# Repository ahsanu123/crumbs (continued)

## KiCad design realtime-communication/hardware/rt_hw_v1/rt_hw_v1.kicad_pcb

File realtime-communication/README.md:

## SDMMC and SDIO 

[See Kicad Project](https://kicanvas.org/?repo=https%3A%2F%2Fgithub.com%2Fahsanu123%2Fcrumbs%2Ftree%2Fmain%2Frealtime-communication%2Fhardware%2Frt_hw_v1)

SDMMC is hardware host, and SDIO is the protocol. 

- look at esp32 [SDMMC documentation here](https://docs.espressif.com/projects/rust/esp-hal/1.2.0/esp32s3/esp_hal/sdmmc/index.html)
- working POC in STM32F407VGT6 is use this _file system_ [exfat-slim](https://github.com/ninjasource/exfat-slim/tree/main),
  poc already prof library able to reading and writing into file. 
- make sure to format sdcard to exfat file system, use this command below, make sure you install required dependencies 
  - install with pacman `sudo pacman -S exfatprogs parted dosfstools `
  - use `lsblk` to list all possible sdcard
  - replace _X_ to possible sdcard listed from lsblk 
  - `sudo umount /dev/sdX*`
  - `sudo wipefs -a /dev/sdX`
  - `sudo parted /dev/sdX --script mklabel msdos`
  - `sudo parted /dev/sdX --script mkpart primary 1MiB 100%`
  - `sudo mkfs.exfat -n SDCARD /dev/sdX1`
  - `sync`
  - then check with, make sure you see exfat on command result
  - `lsblk -f /dev/sdX`
  - `sudo file -s /dev/sdX1`

## Reference 

- https://github.com/zpg6/esp32-sdcard/
- https://docs.rs/embedded-sdmmc/latest/embedded_sdmmc/
- https://github.com/ninjasource/exfat-slim/tree/main
- https://github.com/embassy-rs/sdio

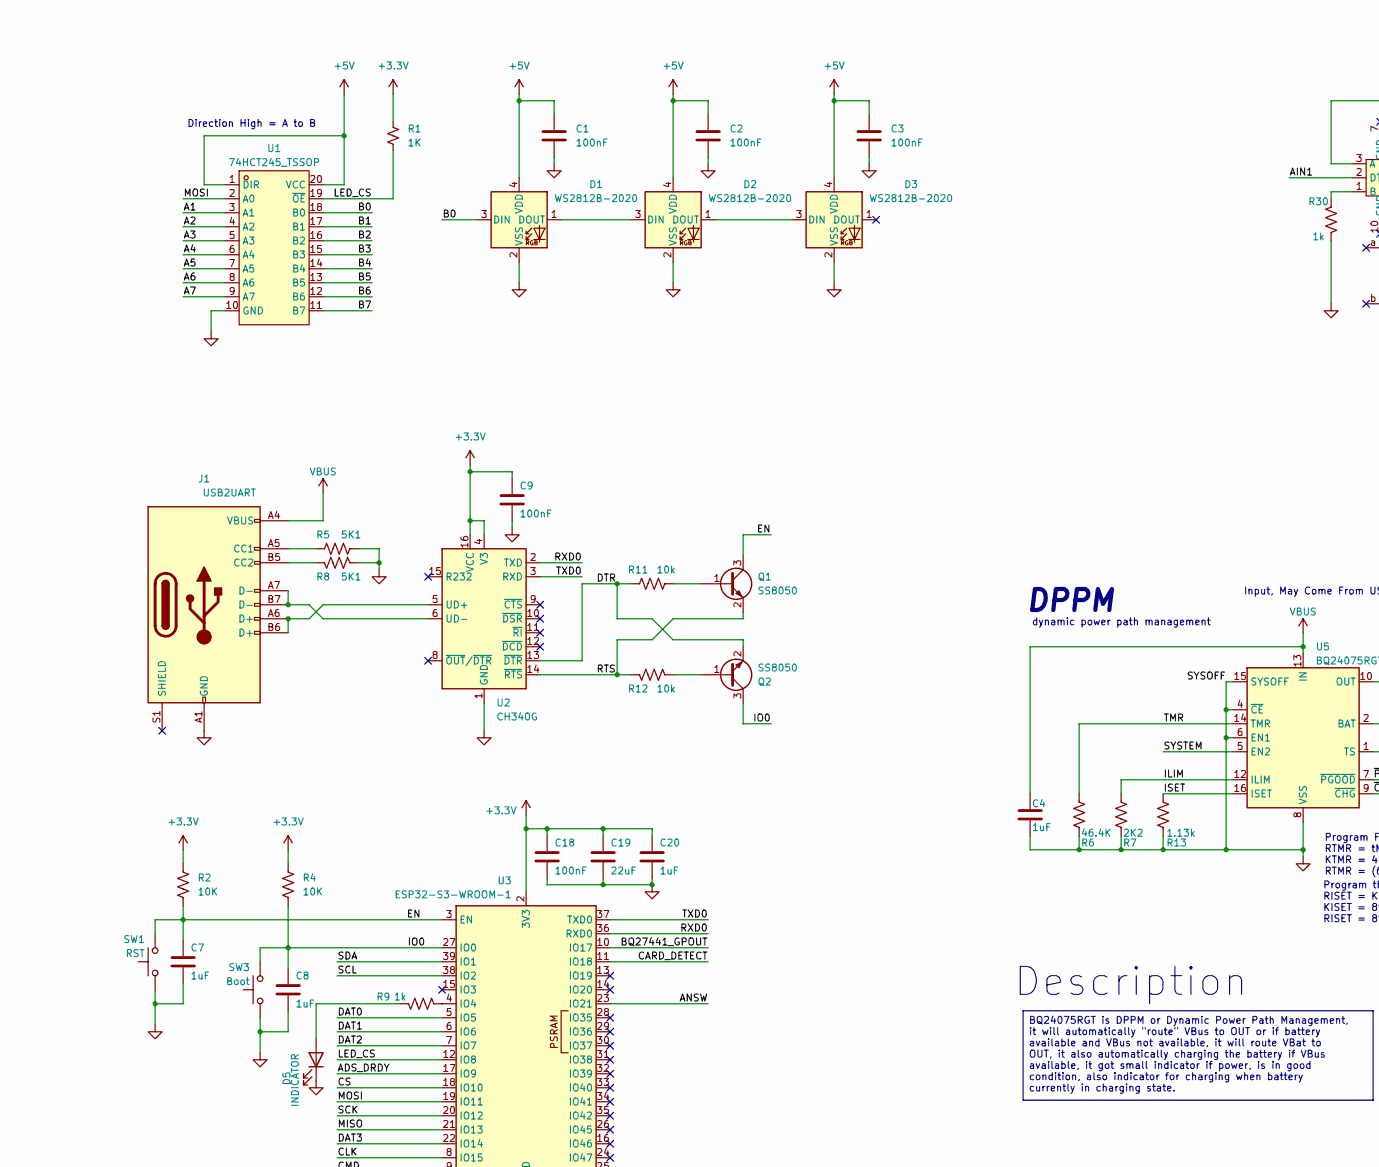
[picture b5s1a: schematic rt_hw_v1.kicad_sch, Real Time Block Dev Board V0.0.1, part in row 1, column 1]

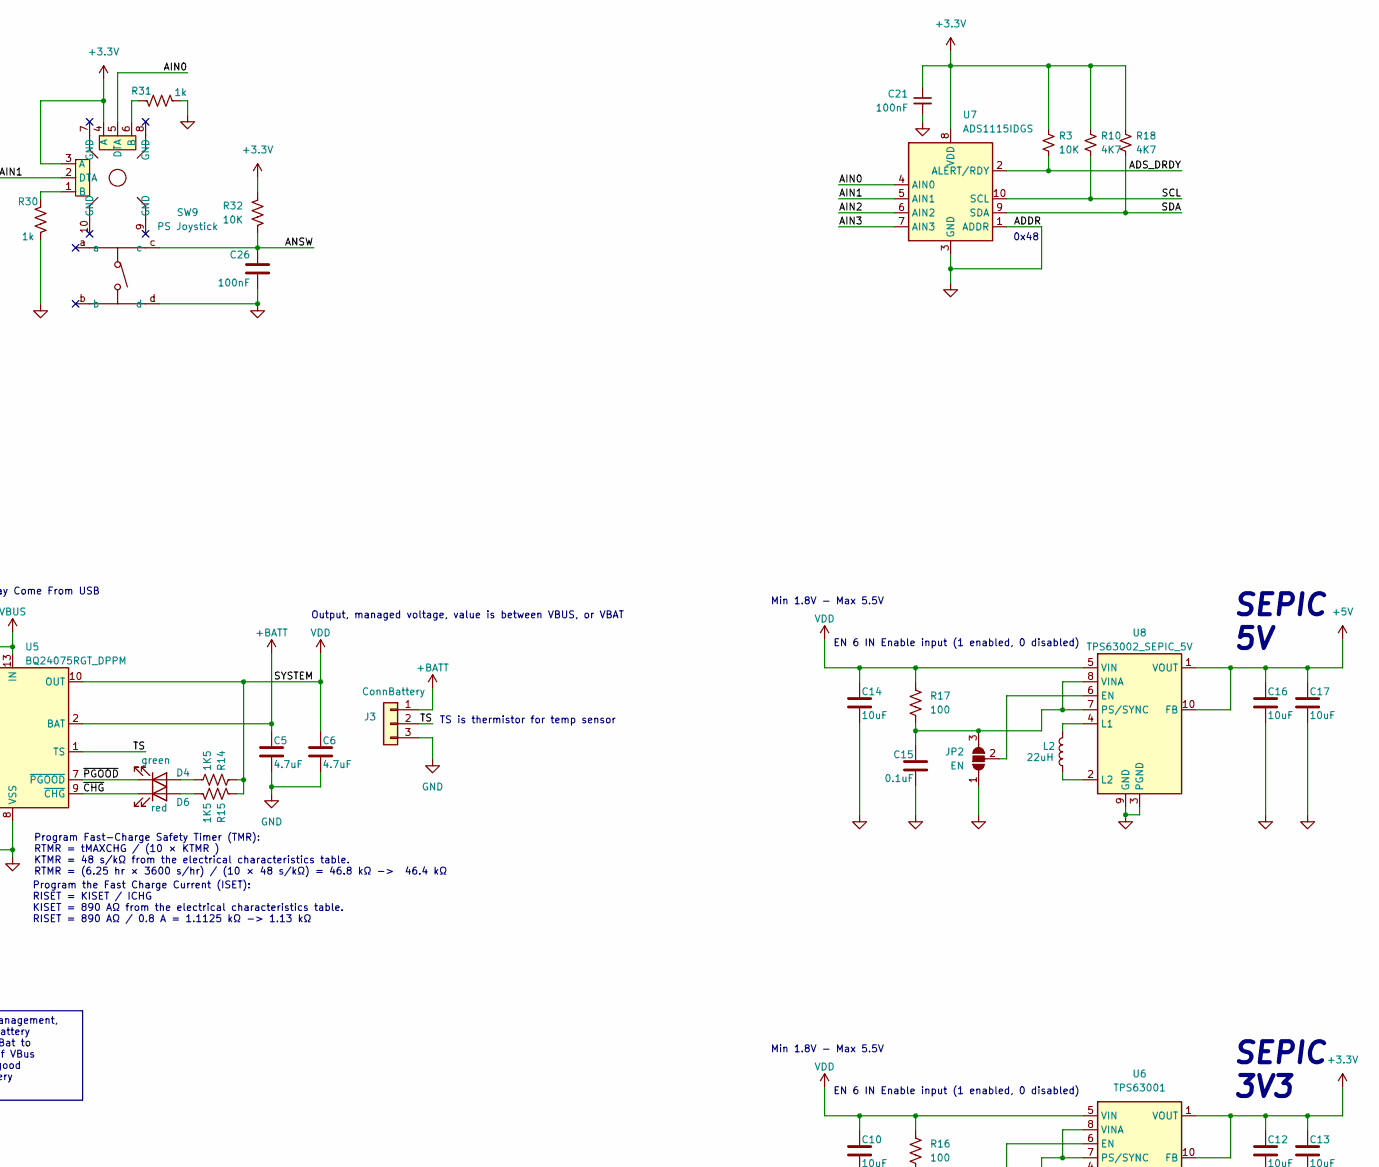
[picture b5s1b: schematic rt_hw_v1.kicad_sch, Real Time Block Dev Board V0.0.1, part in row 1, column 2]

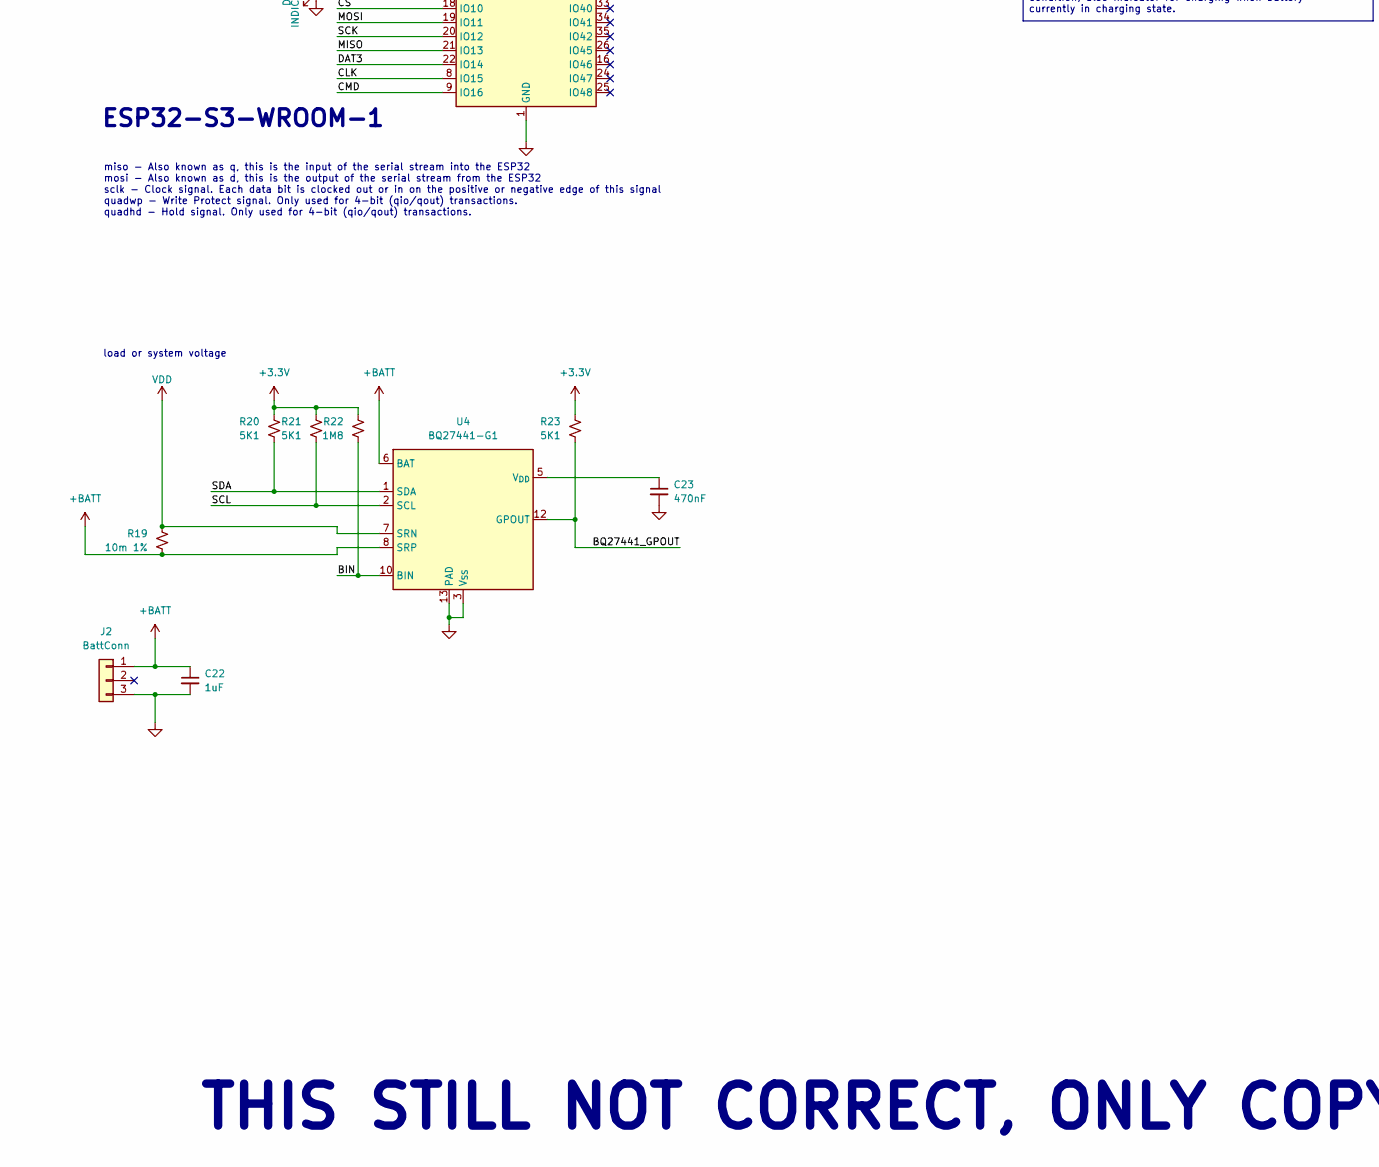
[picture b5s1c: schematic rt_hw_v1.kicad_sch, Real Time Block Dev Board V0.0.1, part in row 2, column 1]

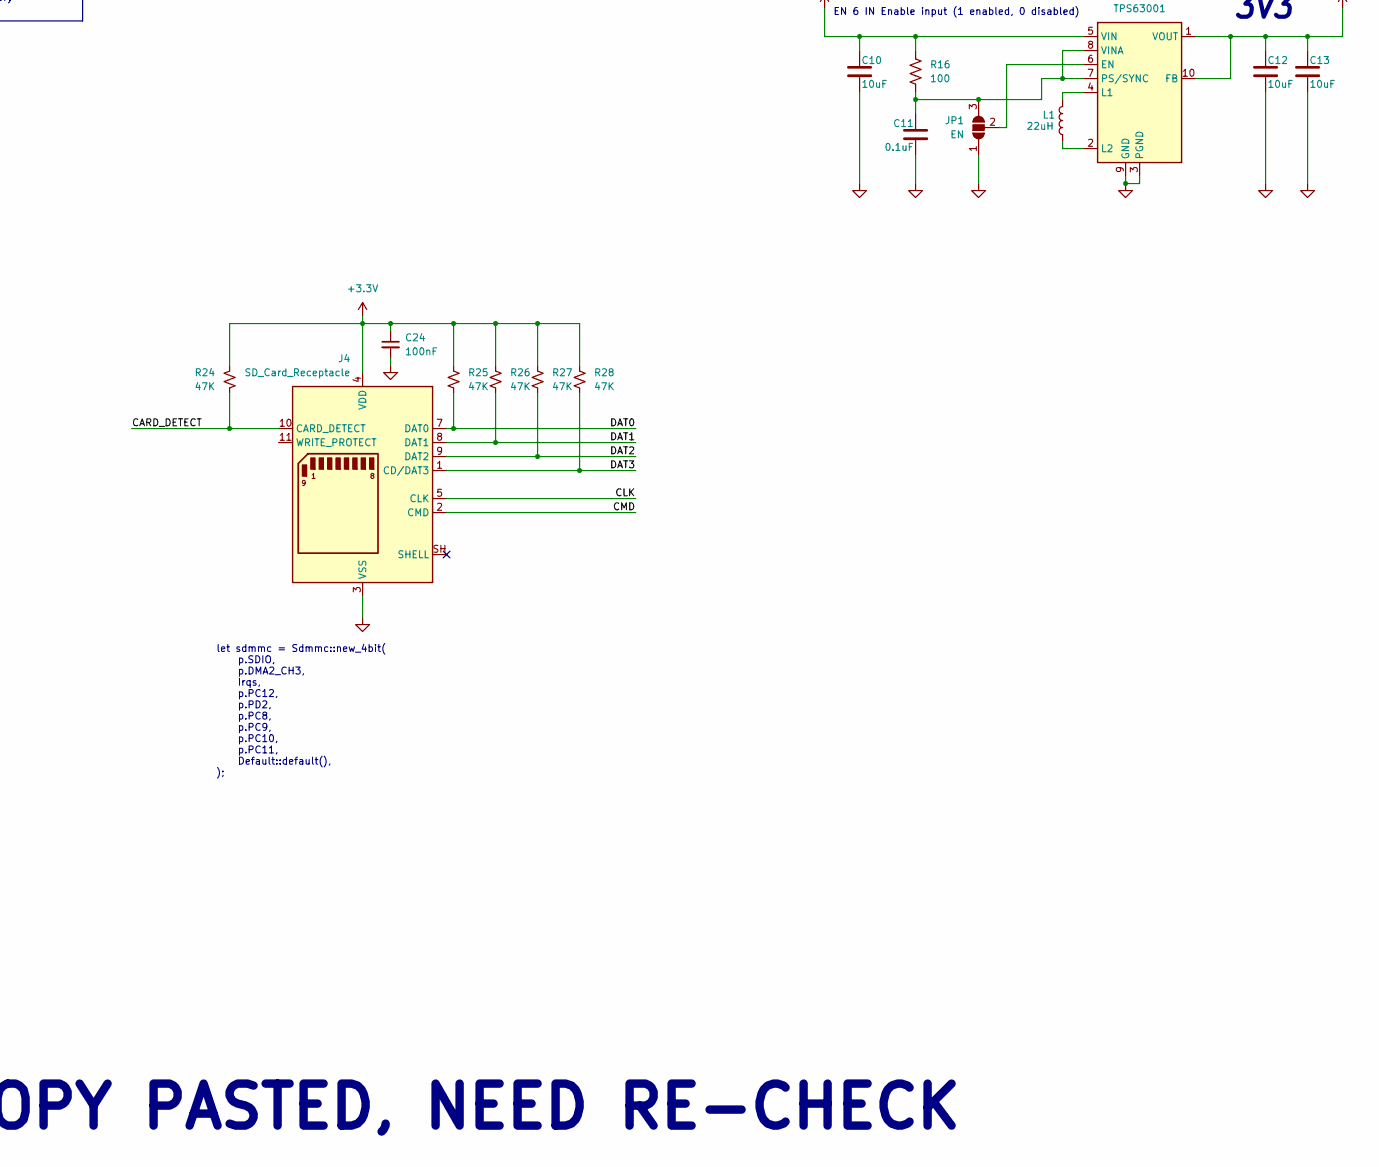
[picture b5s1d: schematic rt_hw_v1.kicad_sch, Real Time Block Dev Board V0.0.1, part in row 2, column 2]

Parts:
C1, C2, C3, C21, C24: 100nF; C_0805_2012Metric
C4, C7, C8, C20: 1uF; C_0805_2012Metric_Pad1.18x1.45mm_HandSolder
C5, C6: 4.7uF; C_0805_2012Metric_Pad1.18x1.45mm_HandSolder
C9, C18, C26: 100nF; C_0805_2012Metric_Pad1.18x1.45mm_HandSolder
C10, C12, C13, C14, C16, C17: 10uF; C_0805_2012Metric_Pad1.18x1.45mm_HandSolder
C11, C15: 0.1uF; C_0805_2012Metric_Pad1.18x1.45mm_HandSolder
C19: 22uF; C_0805_2012Metric_Pad1.18x1.45mm_HandSolder
C22: 1uF; C_0805_2012Metric
C23: 470nF; C_0805_2012Metric
D1, D2, D3: WS2812B-2020; LED_WS2812B-2020_PLCC4_2.0x2.0mm
D4: green; LED_0805_2012Metric_Pad1.15x1.40mm_HandSolder
D5: INDICATOR; LED_1206_3216Metric_Pad1.42x1.75mm_HandSolder
D6: red; LED_0805_2012Metric_Pad1.15x1.40mm_HandSolder
J1: USB2UART; USB_C_Receptacle_GCT_USB4110
J2: BattConn; PinSocket_1x03_P2.54mm_Vertical
J3: ConnBattery; PinHeader_1x03_P2.54mm_Vertical
J4: SD_Card_Receptacle; SD_TE_2041021
JP1, JP2: EN; SolderJumper-3_P1.3mm_Open_RoundedPad1.0x1.5mm_NumberLabels
L1, L2: 22uH; L_Bourns_SRP7028A_7.3x6.6mm
Q1, Q2: SS8050; SOT-23_Handsoldering
R1: 1K; R_0805_2012Metric
R2, R4, R32: 10K; R_0805_2012Metric_Pad1.20x1.40mm_HandSolder
R3: 10K; R_0805_2012Metric
R5, R8: 5K1; R_0805_2012Metric_Pad1.20x1.40mm_HandSolder
R6: 46.4K; R_0805_2012Metric_Pad1.20x1.40mm_HandSolder
R7: 2K2; R_0805_2012Metric_Pad1.20x1.40mm_HandSolder
R9, R30, R31: 1k; R_0805_2012Metric_Pad1.20x1.40mm_HandSolder
R10, R18: 4K7; R_0805_2012Metric
R11, R12: 10k; R_0805_2012Metric_Pad1.20x1.40mm_HandSolder
R13: 1.13k; R_0805_2012Metric_Pad1.20x1.40mm_HandSolder
R14, R15: 1K5; R_0805_2012Metric_Pad1.20x1.40mm_HandSolder
R16, R17: 100; R_0805_2012Metric_Pad1.20x1.40mm_HandSolder
R19: 10m 1%; R_0805_2012Metric
R20, R21, R23: 5K1; R_0805_2012Metric
R22: 1M8; R_0805_2012Metric
R24, R25, R26, R27, R28: 47K; R_0805_2012Metric
SW1: RST; SW_SPST_PTS810
SW3: Boot; SW_SPST_PTS810
SW9: PS Joystick; SW-TH_RKJXV1224005; MPN RKJXV1224005; LCSC Part C146170
U1: 74HCT245_TSSOP; TSSOP-20_L6.5-W4.4-P0.65-LS6.4-BL; MPN 74HCT245PW; LCSC Part C52140501
U2: CH340G; SOIC-16_3.9x9.9mm_P1.27mm
U3: ESP32-S3-WROOM-1
U4: BQ27441-G1; Texas_S-PDSO-N12
U5: BQ24075RGT_DPPM; VQFN-16-1EP_3x3mm_P0.5mm_EP1.6x1.6mm
U6: TPS63001; Texas_DRC0010J_ThermalVias
U7: ADS1115IDGS; TSSOP-10_3x3mm_P0.5mm
U8: TPS63002_SEPIC_5V; Texas_DRC0010J_ThermalVias

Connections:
+3.3V: C9.1, C12.1, C13.1, C18.1, C19.1, C20.1, C21.1, C24.1, J4.4 (VDD), R1.1, R2.1, R3.1, R4.1, R10.1, R18.1, R20.1, R21.1, R22.1, R23.1, R24.1, R25.1, R26.1, R27.1, R28.1, R32.1, SW9.3 (A), SW9.4 (A), U2.4 (V3), U2.16 (VCC), U3.2 (3V3), U6.1 (VOUT), U6.10 (FB), U7.8 (VDD)
+5V: C1.1, C2.1, C3.1, C16.1, C17.1, D1.4 (VDD), D2.4 (VDD), D3.4 (VDD), U1.1 (DIR), U1.20 (VCC), U8.1 (VOUT), U8.10 (FB)
+BATT: C5.1, C22.1, J2.1, J3.1, R19.2, U4.6 (BAT), U4.8 (SRP), U5.2 (BAT), U5.3 (BAT)
/A1: U1.3 (A1)
/A2: U1.4 (A2)
/A3: U1.5 (A3)
/A4: U1.6 (A4)
/A5: U1.7 (A5)
/A6: U1.8 (A6)
/A7: U1.9 (A7)
/ADS_DRDY: R3.2, U3.17 (IO9), U7.2 (ALERT/RDY)
/AIN0: SW9.5 (DTA), U7.4 (AIN0)
/AIN1: SW9.2 (DTA), U7.5 (AIN1)
/AIN2: U7.6 (AIN2)
/AIN3: U7.7 (AIN3)
/ANSW: C26.1, R32.2, SW9.c, U3.23 (IO21)
/B0: D1.3 (DIN), U1.18 (B0)
/B1: U1.17 (B1)
/B2: U1.16 (B2)
/B3: U1.15 (B3)
/B4: U1.14 (B4)
/B5: U1.13 (B5)
/B6: U1.12 (B6)
/B7: U1.11 (B7)
/BIN: R22.2, U4.10 (BIN)
/BQ27441_GPOUT: R23.2, U3.10 (IO17), U4.12 (GPOUT)
/CARD_DETECT: J4.10 (CARD_DETECT), R24.2, U3.11 (IO18)
/CLK: J4.5 (CLK), U3.8 (IO15)
/CMD: J4.2 (CMD), U3.9 (IO16)
/CS: U3.18 (IO10)
/DAT0: J4.7 (DAT0), R25.2, U3.5 (IO5)
/DAT1: J4.8 (DAT1), R26.2, U3.6 (IO6)
/DAT2: J4.9 (DAT2), R27.2, U3.7 (IO7)
/DAT3: J4.1 (CD/DAT3), R28.2, U3.22 (IO14)
/DTR: Q2.2 (E), R11.2, U2.13 (~DTR)
/EN: C7.1, Q1.3 (C), R2.2, SW1.2, U3.3 (EN)
/ILIM: R7.1, U5.12 (ILIM)
/IO0: C8.1, Q2.3 (C), R4.2, SW3.2, U3.27 (IO0)
/ISET: R13.1, U5.16 (ISET)
/LED_CS: R1.2, U1.19 (~OE), U3.12 (IO8)
/MISO: U3.21 (IO13)
/MOSI: U1.2 (A0), U3.19 (IO11)
/RTS: Q1.2 (E), R12.2, U2.14 (~RTS)
/RXD0: U2.2 (TXD), U3.36 (RXD0)
/SCK: U3.20 (IO12)
/SCL: R10.2, R21.2, U3.38 (IO2), U4.2 (SCL), U7.10 (SCL)
/SDA: R18.2, R20.2, U3.39 (IO1), U4.1 (SDA), U7.9 (SDA)
/TMR: R6.1, U5.14 (TMR)
/TS: J3.2, U5.1 (TS)
/TXD0: U2.3 (RXD), U3.37 (TXD0)
/~CHG: D6.1 (K), U5.9 (~CHG)
/~PGOOD: D4.1 (K), U5.7 (~PGOOD)
GND: C1.2, C2.2, C3.2, C4.2, C5.2, C6.2, C7.2, C8.2, C9.2, C10.2, C11.2, C12.2, C13.2, C14.2, C15.2, C16.2, C17.2, C18.2, C19.2, C20.2, C21.2, C22.2, C23.2, C24.2, C26.2, D1.2 (VSS), D2.2 (VSS), D3.2 (VSS), D5.1 (K), J1.A1 (GND), J1.A12 (GND), J1.B1 (GND), J1.B12 (GND), J2.3, J3.3, J4.3 (VSS), J4.6 (VSS), JP1.1 (A), JP2.1 (A), R5.1, R6.2, R7.2, R8.1, R13.2, R30.1, R31.2, SW1.1, SW3.1, SW9.d, U1.10 (GND), U2.1 (GND), U3.1 (GND), U3.40 (GND), U3.41 (GND), U4.3 (V_{SS}), U4.13 (PAD), U5.4 (~CE), U5.6 (EN1), U5.8 (VSS), U5.15 (SYSOFF), U5.17 (VSS), U6.3 (PGND), U6.9 (GND), U6.11 (PGND), U7.1 (ADDR), U7.3 (GND), U8.3 (PGND), U8.9 (GND), U8.11 (PGND)
unnamed: D1.1 (DOUT), D2.3 (DIN)
unnamed: D2.1 (DOUT), D3.3 (DIN)
unnamed: D4.2 (A), R14.1
unnamed: D5.2 (A), R9.1
unnamed: D6.2 (A), R15.1
unnamed: J1.A5 (CC1), R5.2
unnamed: J1.B5 (CC2), R8.2
unnamed: C11.1, JP1.3 (B), R16.2, U6.7 (PS/SYNC), U6.8 (VINA)
unnamed: JP1.2 (C), U6.6 (EN)
unnamed: C15.1, JP2.3 (B), R17.2, U8.7 (PS/SYNC), U8.8 (VINA)
unnamed: JP2.2 (C), U8.6 (EN)
unnamed: Q1.1 (B), R11.1
unnamed: Q2.1 (B), R12.1
unnamed: R30.2, SW9.1 (B)
unnamed: R31.1, SW9.6 (B)
unnamed: J1.A6 (D+), J1.B6 (D+), U2.5 (UD+)
unnamed: J1.A7 (D-), J1.B7 (D-), U2.6 (UD-)
unnamed: R9.2, U3.4 (IO4)
unnamed: C23.1, U4.5 (V_{DD})
unnamed: L1.2, U6.4 (L1)
unnamed: L1.1, U6.2 (L2)
unnamed: L2.2, U8.4 (L1)
unnamed: L2.1, U8.2 (L2)
VBUS: C4.1, J1.A4 (VBUS), J1.A9 (VBUS), J1.B4 (VBUS), J1.B9 (VBUS), U5.13 (IN)
VDD: C6.1, C10.1, C14.1, R14.2, R15.2, R16.1, R17.1, R19.1, U4.7 (SRN), U5.5 (EN2), U5.10 (OUT), U5.11 (OUT), U6.5 (VIN), U8.5 (VIN)

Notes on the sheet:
Output, managed voltage, value is between VBUS, or VBAT
SEPIC 3V3
ESP32-S3-WROOM-1
DPPM
Min 1.8V - Max 5.5V
THIS STILL NOT CORRECT, ONLY COPY PASTED, NEED RE-CHECK
let sdmmc = Sdmmc::new_4bit( p.SDIO, p.DMA2_CH3, Irqs, p.PC12, p.PD2, p.PC8, p.PC9, p.PC10, p.PC11, Default::default(), );
EN 6 IN Enable input (1 enabled, 0 disabled)
dynamic power path management
miso - Also known as q, this is the input of the serial stream into the ESP32 mosi - Also known as d, this is the output of the serial stream from the ESP32 sclk - Clock signal. Each data bit is clocked out or in on the positive or negative edge of this signal quadwp - Write Protect signal. Only us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
Input, May Come From USB
Program the Fast Charge Current (ISET): RISET = KISET / ICHG KISET = 890 AΩ from the electrical characteristics table. RISET = 890 AΩ / 0.8 A = 1.1125 kΩ -> 1.13 kΩ
load or system voltage
Direction High = A to B
0x48
Program Fast-Charge Safety Timer (TMR): RTMR = tMAXCHG / (10 × KTMR ) KTMR = 48 s/kΩ from the electrical characteristics table. RTMR = (6.25 hr × 3600 s/hr) / (10 × 48 s/kΩ) = 46.8 kΩ -> 46.4 kΩ
Description
TS is thermistor for temp sensor
SEPIC 5V
BQ24075RGT is DPPM or Dynamic Power Path Management, it will automatically "route" VBus to OUT or if battery available and VBus not available, it will route VBat to OUT, it also automatically charging the battery if VBus available, it got small indicator if power, is in good condition, also indicat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

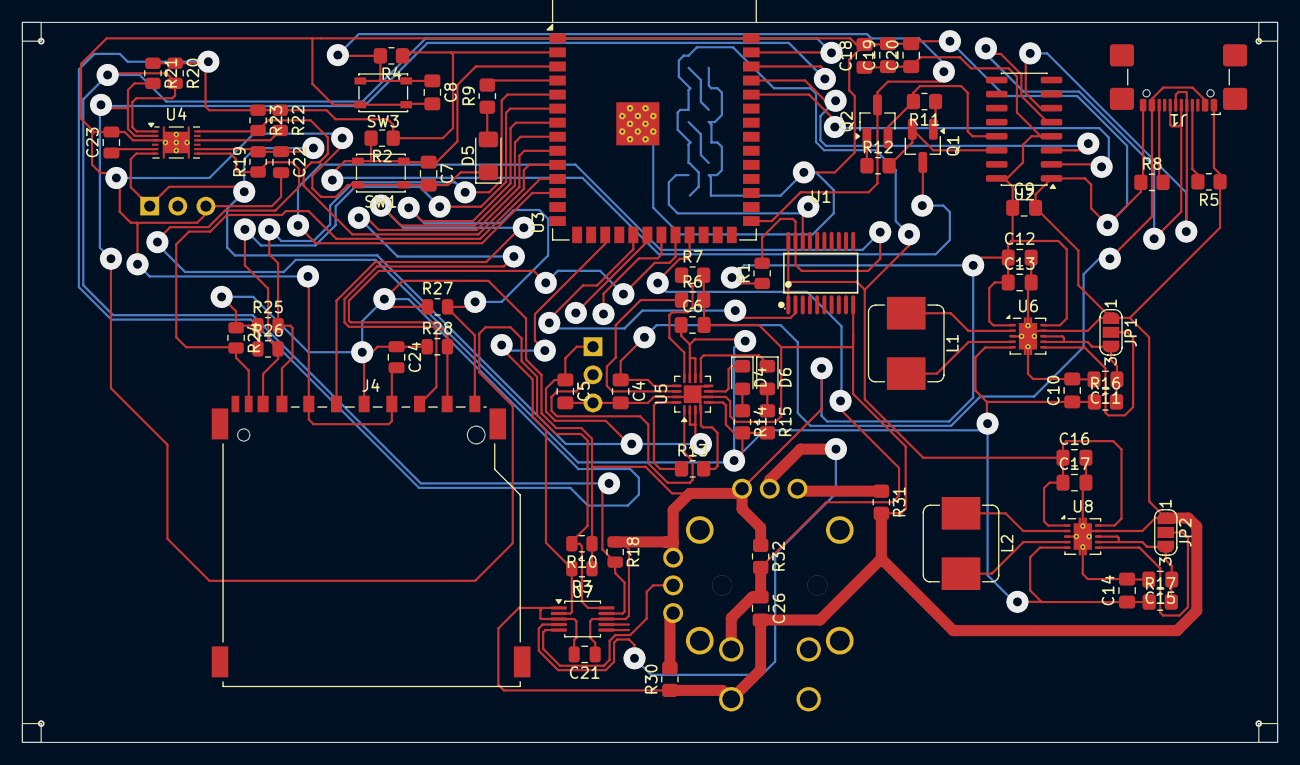
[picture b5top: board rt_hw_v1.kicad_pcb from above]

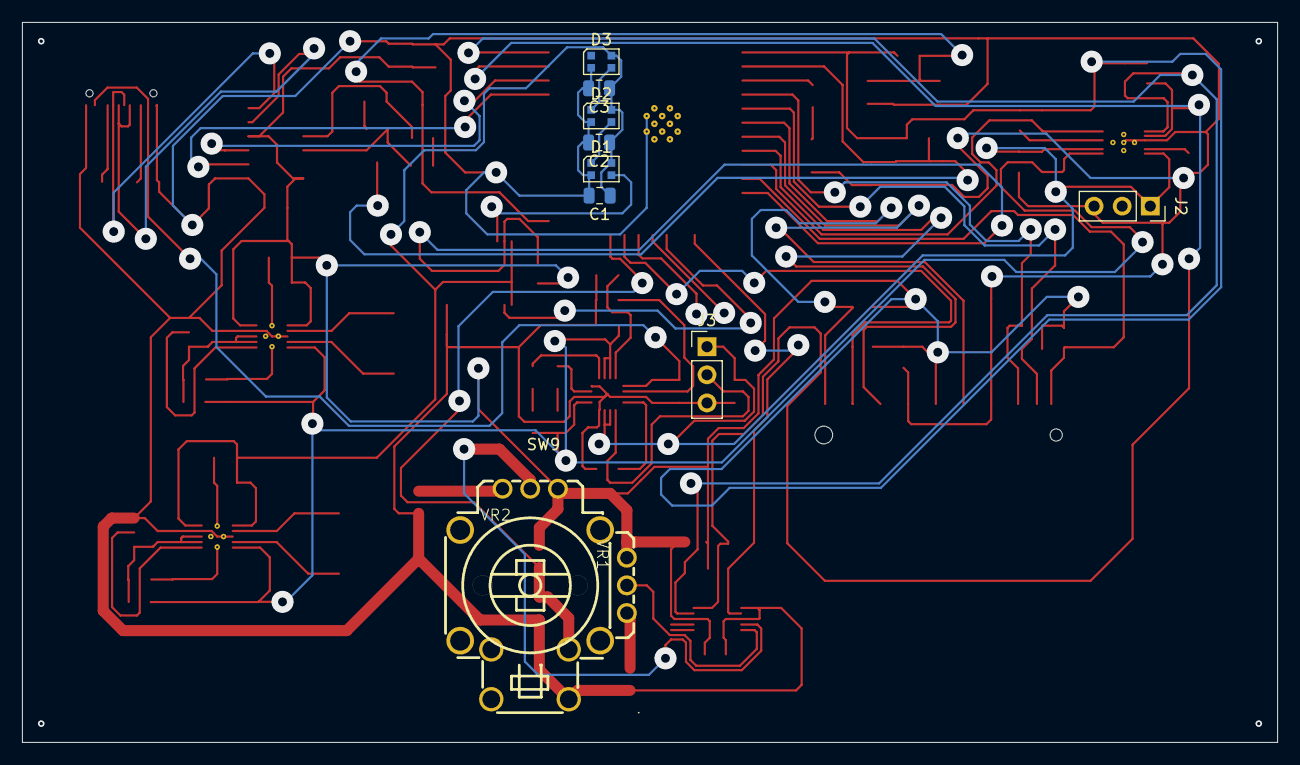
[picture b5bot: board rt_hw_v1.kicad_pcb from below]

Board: 2 copper layers, 113.4 x 65.0 mm, 83 parts (9 on the bottom side), 59 nets.

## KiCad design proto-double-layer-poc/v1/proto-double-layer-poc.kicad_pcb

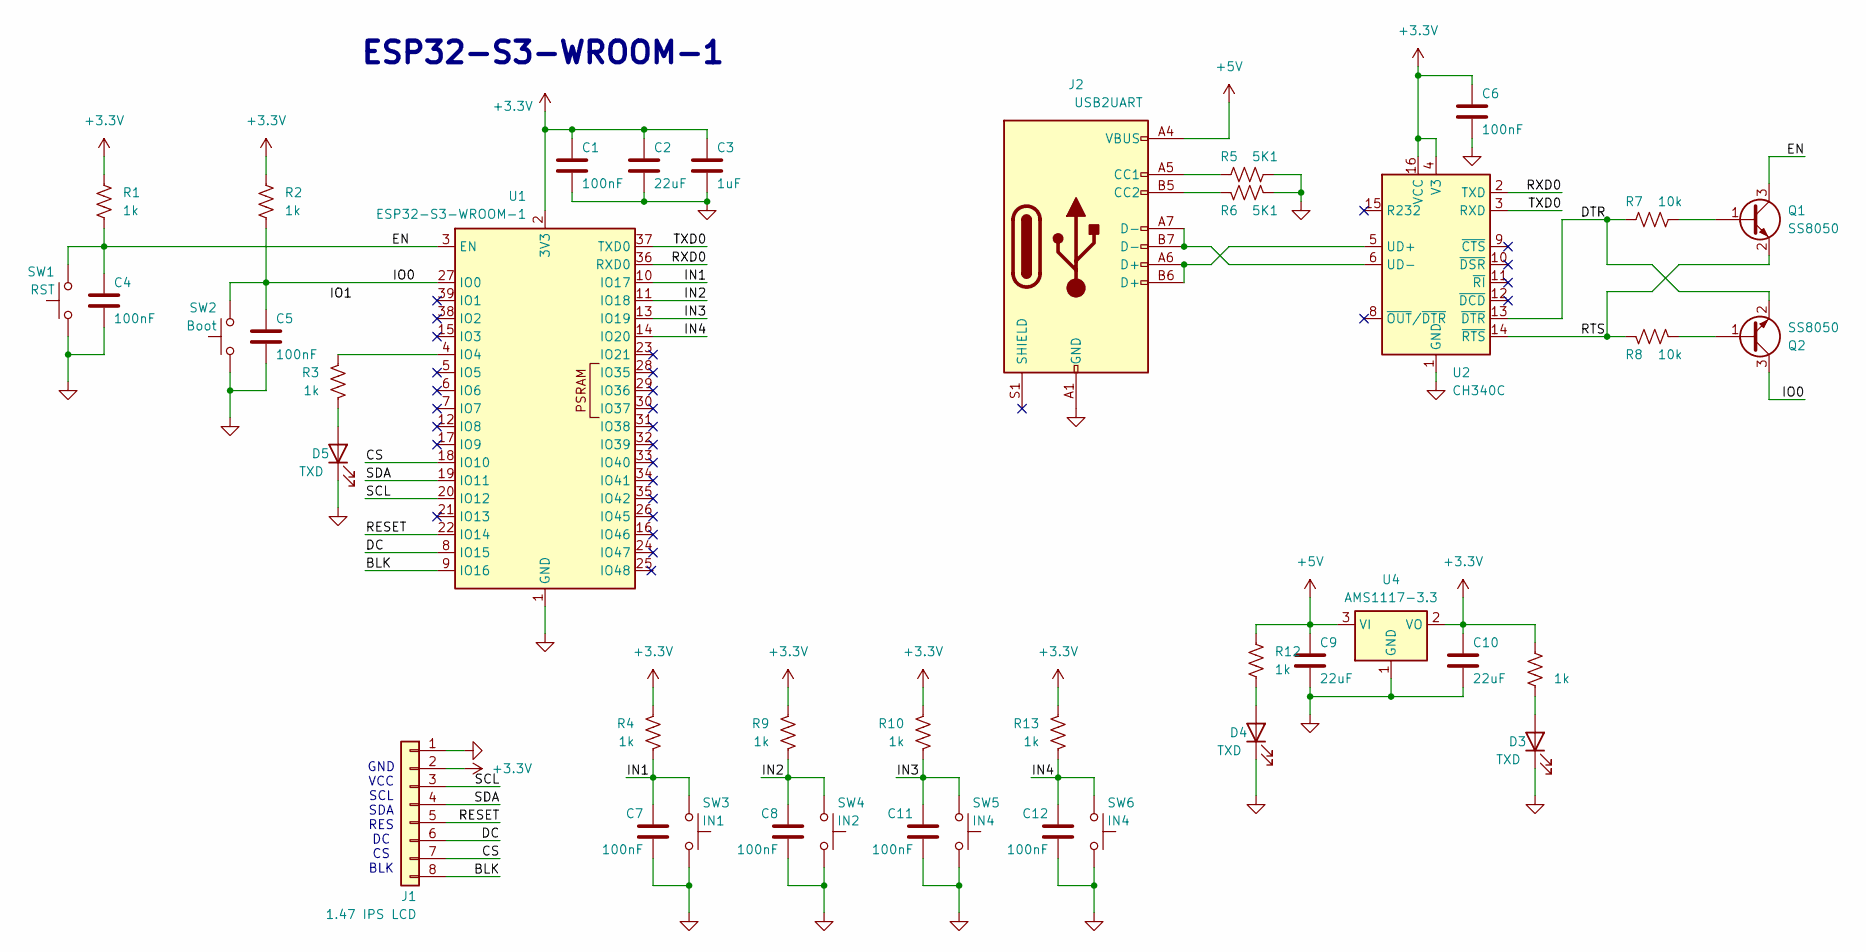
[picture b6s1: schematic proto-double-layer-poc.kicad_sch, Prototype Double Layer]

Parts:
C1, C4, C5, C6, C7, C8, C11, C12: 100nF; C_0805_2012Metric_Pad1.18x1.45mm_HandSolder
C2, C9, C10: 22uF; C_0805_2012Metric_Pad1.18x1.45mm_HandSolder
C3: 1uF; C_0805_2012Metric_Pad1.18x1.45mm_HandSolder
D3, D4, D5: TXD; LED_1206_3216Metric_Pad1.42x1.75mm_HandSolder
J1: 1.47 IPS LCD; PinHeader_1x08_P2.54mm_Vertical
J2: USB2UART; USB_C_Receptacle_GCT_USB4110
Q1, Q2: SS8050; SOT-23_Handsoldering
R1, R2, R3, R4, R9, R10, R11, R12, R13: 1k; R_0805_2012Metric_Pad1.20x1.40mm_HandSolder
R5, R6: 5K1; R_0805_2012Metric_Pad1.20x1.40mm_HandSolder
R7, R8: 10k; R_0805_2012Metric_Pad1.20x1.40mm_HandSolder
SW1: RST; SW_SPST_PTS810
SW2: Boot; SW_SPST_PTS810
SW3: IN1; SW_SPST_PTS810
SW4: IN2; SW_SPST_PTS810
SW5, SW6: IN4; SW_SPST_PTS810
U1: ESP32-S3-WROOM-1
U2: CH340C; SOIC-16_3.9x9.9mm_P1.27mm
U4: AMS1117-3.3; SOT-223-3_TabPin2

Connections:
+3.3V: C1.1, C2.1, C3.1, C6.1, C10.1, J1.2, R1.1, R2.1, R4.1, R9.1, R10.1, R11.1, R13.1, U1.2 (3V3), U2.4 (V3), U2.16 (VCC), U4.2 (VO)
+5V: C9.1, J2.A4 (VBUS), J2.A9 (VBUS), J2.B4 (VBUS), J2.B9 (VBUS), R12.1, U4.3 (VI)
/BLK: J1.8, U1.9 (IO16)
/CS: J1.7, U1.18 (IO10)
/DC: J1.6, U1.8 (IO15)
/DTR: Q2.2 (E), R7.2, U2.13 (~DTR)
/EN: C4.1, Q1.3 (C), R1.2, SW1.2, U1.3 (EN)
/IN1: C7.1, R4.2, SW3.2, U1.10 (IO17)
/IN2: C8.1, R9.2, SW4.2, U1.11 (IO18)
/IN3: C11.1, R10.2, SW5.2, U1.13 (IO19)
/IN4: C12.1, R13.2, SW6.2, U1.14 (IO20)
/IO0: C5.1, Q2.3 (C), R2.2, SW2.2, U1.27 (IO0)
/RESET: J1.5, U1.22 (IO14)
/RTS: Q1.2 (E), R8.2, U2.14 (~RTS)
/RXD0: U1.36 (RXD0), U2.2 (TXD)
/SCL: J1.3, U1.20 (IO12)
/SDA: J1.4, U1.19 (IO11), U1.21 (IO13)
/TXD0: U1.37 (TXD0), U2.3 (RXD)
GND: C1.2, C2.2, C3.2, C4.2, C5.2, C6.2, C7.2, C8.2, C9.2, C10.2, C11.2, C12.2, D3.1 (K), D4.1 (K), D5.1 (K), J1.1, J2.A1 (GND), J2.A12 (GND), J2.B1 (GND), J2.B12 (GND), R5.1, R6.1, SW1.1, SW2.1, SW3.1, SW4.1, SW5.1, SW6.1, U1.1 (GND), U1.40 (GND), U1.41 (GND), U2.1 (GND), U4.1 (GND)
unnamed: D3.2 (A), R11.2
unnamed: D4.2 (A), R12.2
unnamed: D5.2 (A), R3.2
unnamed: J2.A5 (CC1), R5.2
unnamed: J2.B5 (CC2), R6.2
unnamed: Q1.1 (B), R7.1
unnamed: Q2.1 (B), R8.1
unnamed: R3.1, U1.4 (IO4)
unnamed: J2.A6 (D+), J2.B6 (D+), U2.5 (UD+)
unnamed: J2.A7 (D-), J2.B7 (D-), U2.6 (UD-)

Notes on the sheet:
GND VCC SCL SDA RES DC CS BLK
ESP32-S3-WROOM-1

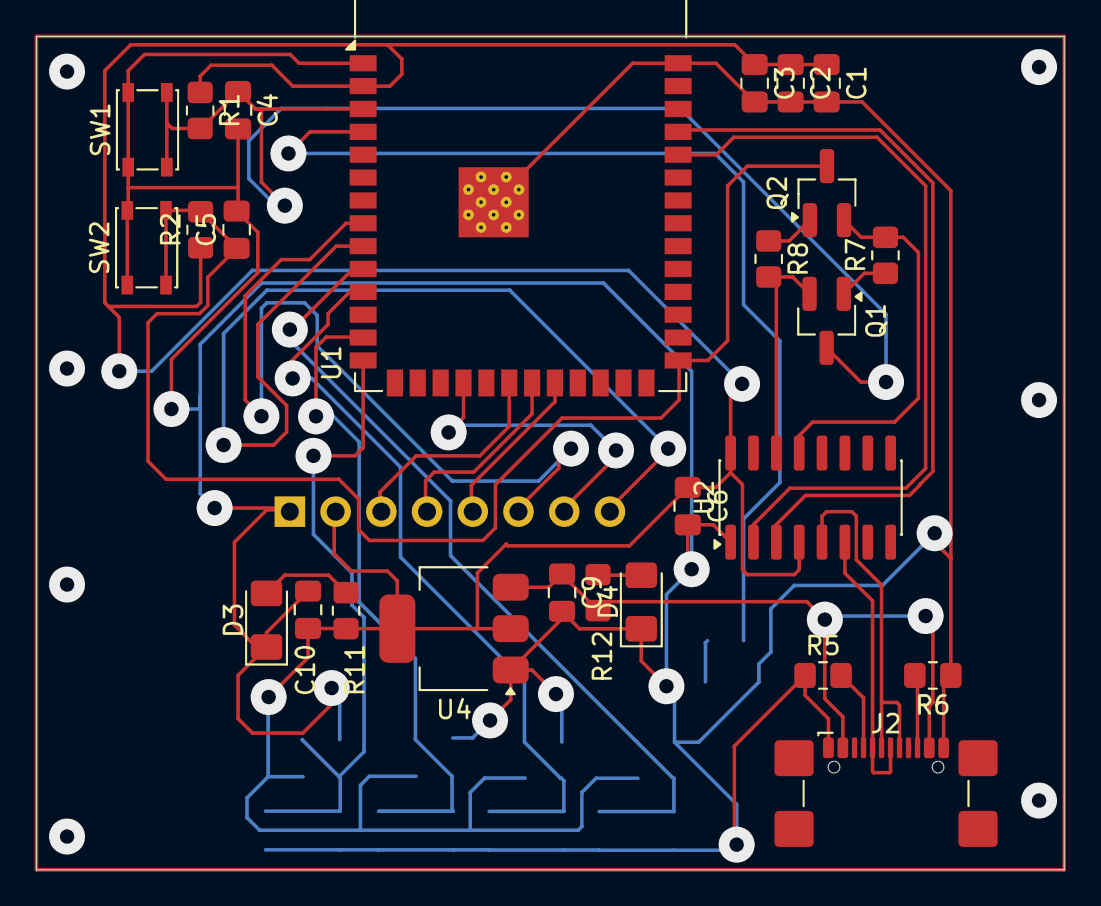
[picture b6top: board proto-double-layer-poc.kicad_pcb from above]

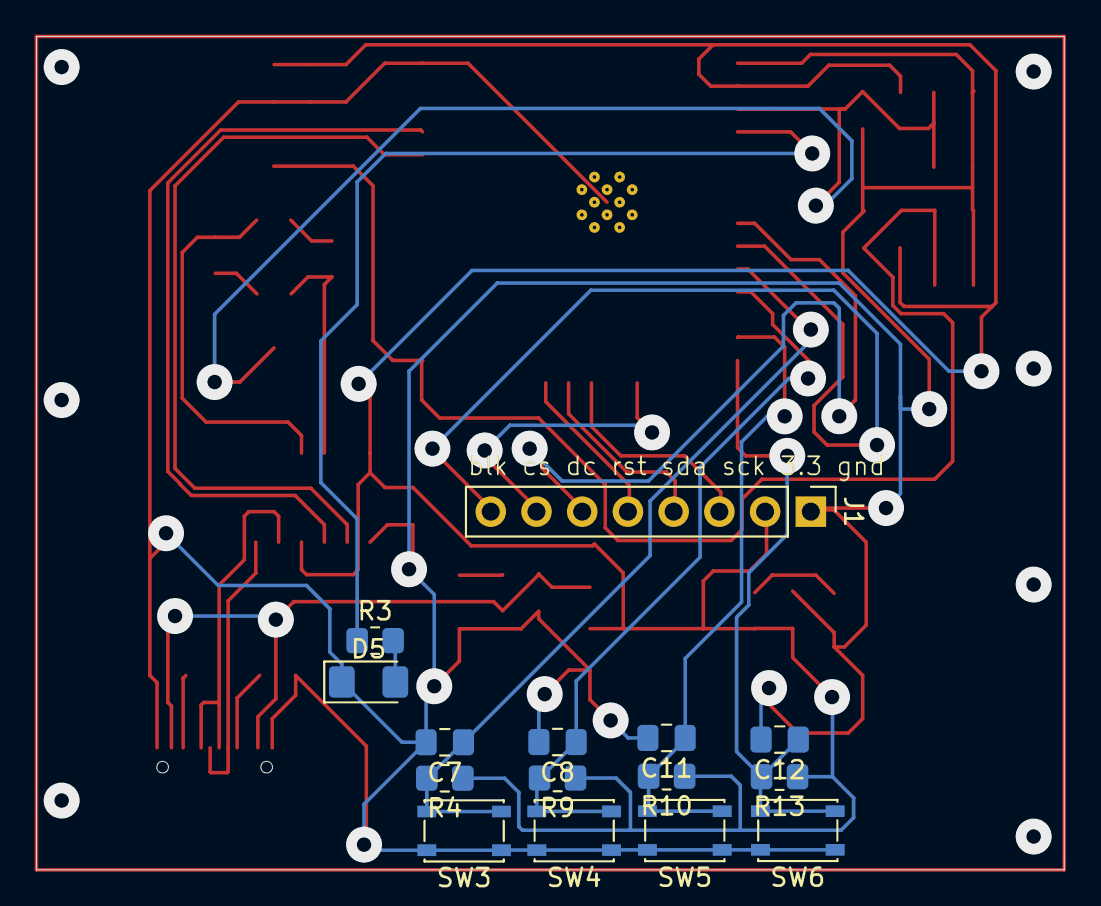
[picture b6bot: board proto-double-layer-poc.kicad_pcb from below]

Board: 2 copper layers, 57.1 x 46.3 mm, 41 parts (15 on the bottom side), 29 nets.

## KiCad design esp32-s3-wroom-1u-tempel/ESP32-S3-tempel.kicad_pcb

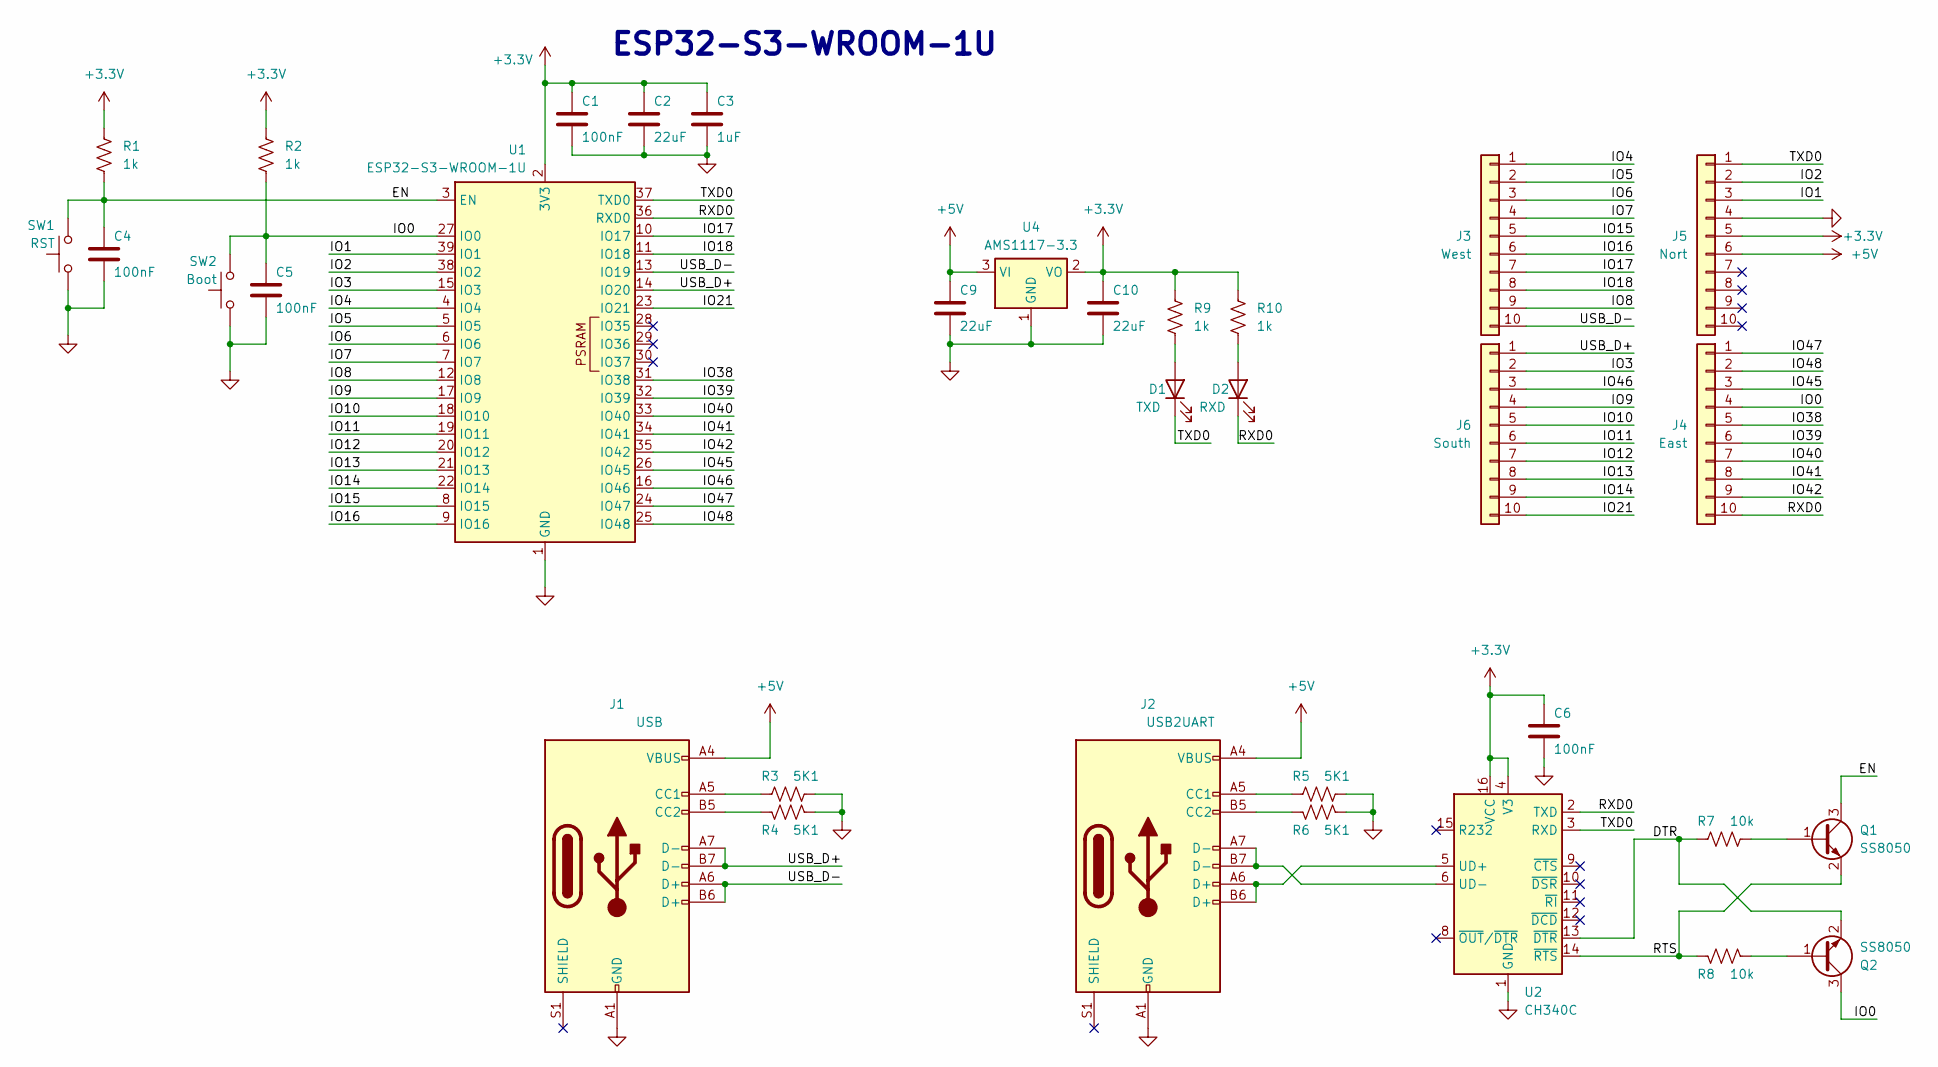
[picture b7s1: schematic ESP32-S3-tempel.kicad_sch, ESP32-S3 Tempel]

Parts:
C1, C4, C5, C6: 100nF; C_0805_2012Metric_Pad1.18x1.45mm_HandSolder
C2, C9, C10: 22uF; C_0805_2012Metric_Pad1.18x1.45mm_HandSolder
C3: 1uF; C_0805_2012Metric_Pad1.18x1.45mm_HandSolder
D1: TXD; LED_1206_3216Metric_Pad1.42x1.75mm_HandSolder
D2: RXD; LED_1206_3216Metric_Pad1.42x1.75mm_HandSolder
J1: USB; USB_C_Receptacle_GCT_USB4110
J2: USB2UART; USB_C_Receptacle_GCT_USB4110
J3: West; PinHeader_1x10_P2.54mm_Vertical
J4: East; PinHeader_1x10_P2.54mm_Vertical
J5: Nort; PinHeader_1x10_P2.54mm_Vertical
J6: South; PinHeader_1x10_P2.54mm_Vertical
Q1, Q2: SS8050; SOT-23_Handsoldering
R1, R2, R9, R10: 1k; R_0805_2012Metric_Pad1.20x1.40mm_HandSolder
R3, R4, R5, R6: 5K1; R_0805_2012Metric_Pad1.20x1.40mm_HandSolder
R7, R8: 10k; R_0805_2012Metric_Pad1.20x1.40mm_HandSolder
SW1: RST; SW_Push_1P1T_NO_6x6mm_H9.5mm
SW2: Boot; SW_Push_1P1T_NO_6x6mm_H9.5mm
U1: ESP32-S3-WROOM-1U
U2: CH340C; SOIC-16_3.9x9.9mm_P1.27mm
U4: AMS1117-3.3; SOT-223-3_TabPin2

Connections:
+3.3V: C1.1, C2.1, C3.1, C6.1, C10.1, J5.5, R1.1, R2.1, R9.1, R10.1, U1.2 (3V3), U2.4 (V3), U2.16 (VCC), U4.2 (VO)
+5V: C9.1, J1.A4 (VBUS), J1.A9 (VBUS), J1.B4 (VBUS), J1.B9 (VBUS), J2.A4 (VBUS), J2.A9 (VBUS), J2.B4 (VBUS), J2.B9 (VBUS), J5.6, U4.3 (VI)
/DTR: Q2.2 (E), R7.2, U2.13 (~DTR)
/EN: C4.1, Q1.3 (C), R1.2, SW1.2, U1.3 (EN)
/IO0: C5.1, J4.4, Q2.3 (C), R2.2, SW2.2, U1.27 (IO0)
/IO1: J5.3, U1.39 (IO1)
/IO2: J5.2, U1.38 (IO2)
/IO3: J6.2, U1.15 (IO3)
/IO4: J3.1, U1.4 (IO4)
/IO5: J3.2, U1.5 (IO5)
/IO6: J3.3, U1.6 (IO6)
/IO7: J3.4, U1.7 (IO7)
/IO8: J3.9, U1.12 (IO8)
/IO9: J6.4, U1.17 (IO9)
/IO10: J6.5, U1.18 (IO10)
/IO11: J6.6, U1.19 (IO11)
/IO12: J6.7, U1.20 (IO12)
/IO13: J6.8, U1.21 (IO13)
/IO14: J6.9, U1.22 (IO14)
/IO15: J3.5, U1.8 (IO15)
/IO16: J3.6, U1.9 (IO16)
/IO17: J3.7, U1.10 (IO17)
/IO18: J3.8, U1.11 (IO18)
/IO21: J6.10, U1.23 (IO21)
/IO38: J4.5, U1.31 (IO38)
/IO39: J4.6, U1.32 (IO39)
/IO40: J4.7, U1.33 (IO40)
/IO41: J4.8, U1.34 (IO41)
/IO42: J4.9, U1.35 (IO42)
/IO45: J4.3, U1.26 (IO45)
/IO46: J6.3, U1.16 (IO46)
/IO47: J4.1, U1.24 (IO47)
/IO48: J4.2, U1.25 (IO48)
/RTS: Q1.2 (E), R8.2, U2.14 (~RTS)
/RXD0: D2.1 (K), J4.10, U1.36 (RXD0), U2.2 (TXD)
/TXD0: D1.1 (K), J5.1, U1.37 (TXD0), U2.3 (RXD)
/USB_D+: J1.A7 (D-), J1.B7 (D-), J6.1, U1.14 (IO20)
/USB_D-: J1.A6 (D+), J1.B6 (D+), J3.10, U1.13 (IO19)
GND: C1.2, C2.2, C3.2, C4.2, C5.2, C6.2, C9.2, C10.2, J1.A1 (GND), J1.A12 (GND), J1.B1 (GND), J1.B12 (GND), J2.A1 (GND), J2.A12 (GND), J2.B1 (GND), J2.B12 (GND), J5.4, R3.1, R4.1, R5.1, R6.1, SW1.1, SW2.1, U1.1 (GND), U1.40 (GND), U1.41 (GND), U2.1 (GND), U4.1 (GND)
unnamed: D1.2 (A), R9.2
unnamed: D2.2 (A), R10.2
unnamed: J1.A5 (CC1), R3.2
unnamed: J1.B5 (CC2), R4.2
unnamed: J2.A5 (CC1), R5.2
unnamed: J2.B5 (CC2), R6.2
unnamed: Q1.1 (B), R7.1
unnamed: Q2.1 (B), R8.1
unnamed: J2.A6 (D+), J2.B6 (D+), U2.5 (UD+)
unnamed: J2.A7 (D-), J2.B7 (D-), U2.6 (UD-)

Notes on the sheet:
ESP32-S3-WROOM-1U
